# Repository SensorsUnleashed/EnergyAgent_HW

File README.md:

# EnergyAgent_HW
Used for the unleased network. Can measure energy consumption and turn on/off appliances - all done in an if/then/do kind of way

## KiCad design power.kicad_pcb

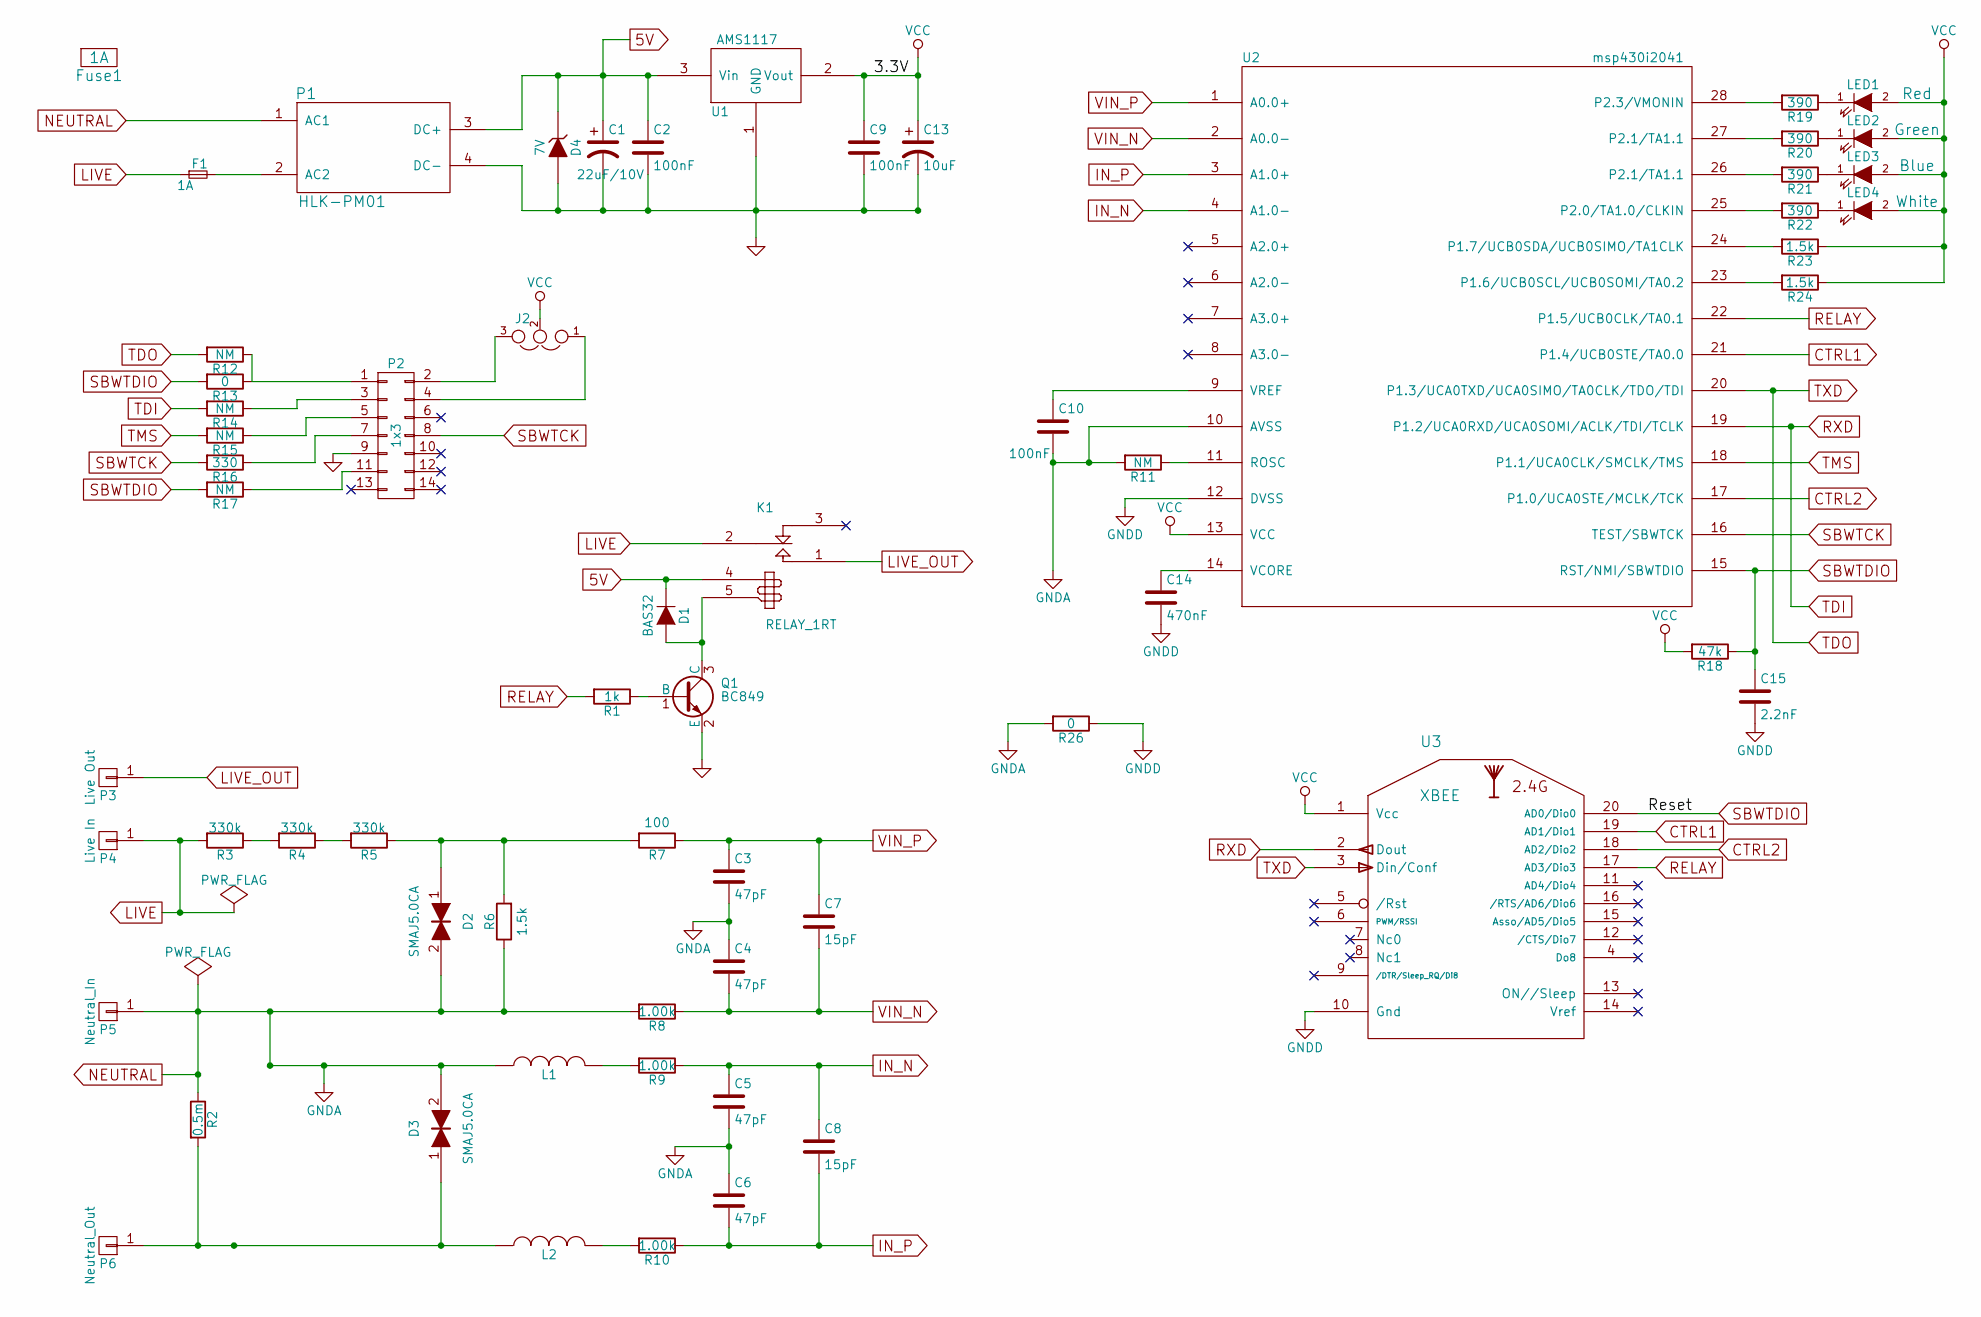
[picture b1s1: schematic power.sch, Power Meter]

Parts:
C1: 22uF/10V; C_0805
C2, C9, C10: 100nF; C_0805
C3, C4, C5, C6: 47pF; C_0805
C7, C8: 15pF; C_0805
C13: 10uF; TantalC_SizeT_EIA-3528; Manufacturer Part Number 293D106X0010B2TE3
C14: 470nF; C_0805
C15: 2.2nF; C_0805; Manufacturer Part Number 0805ZC222JAT2A
D1: BAS32; SOD-323; Manufacturer Part Number BAS321,115
D2, D3: SMAJ5.0CA; SMA_Standard; Manufacturer Part Number SMAJ5.0CA
D4: 7V; SMB_Standard; Manufacturer Part Number SMBJ7.0A-FDICT-ND
F1: 1A; Fuseholder5x20_horiz_open_Schurter_0031_8201; Manufacturer Part Number 0031.8201
Fuse1: 1A; Manufacturer Part Number 0034.3117
J2: JUMPER3; Pin_Header_Straight_1x03; Manufacturer Part Number S1011E-03-ND
K1: RELAY_1RT; Relay_SRD_XVDC-SL-C_SeriesPin4-5Swap; Manufacturer Part Number SRD-5VDC-SL-C
L1, L2: INDUCTOR; R_0805; Manufacturer Part Number BLM21BD121SN1D
LED1: LED; LED_0805; Manufacturer Part Number LTST-C170KRKT
LED2: LED; LED_0805; Manufacturer Part Number LTST-S220KGKT
LED3: LED; LED_0805; Manufacturer Part Number LTST-C170TBKT
LED4: LED4; LED_0805; Manufacturer Part Number LTW-170TK
P1: HLK-PM01
P2: 1x3; IDC_Header_Straight_14pins; Manufacturer Part Number 1-1634688-4
P3: Live Out; Banana_Jack_1Pin
P4: Live In; Banana_Jack_1Pin
P5: Neutral_In; Banana_Jack_1Pin
P6: Neutral_Out; Banana_Jack_1Pin
Q1: BC849; SOT-23
R1: 1k; R_0805
R2: 0.5m; R_2512_current_sense_4_wire; Manufacturer Part Number ULRB12512R0005FLFSLT
R3, R4, R5: 330k; R_2010; Manufacturer Part Number ERJ-S1DF3303U
R6: 1.5k; R_2010; Manufacturer Part Number MCR50JZHF1501
R7: 100; R_0805
R8, R9, R10: 1.00k; R_0805
R11, R12, R14, R15, R17: NM; R_0805
R13, R26: 0; R_0805
R16: 330; R_0805
R18: 47k; R_0805
R19, R20, R21, R22: 390; R_0805; Manufacturer Part Number ERJ-6GEYJ391V
R23, R24: 1.5k; R_0805
U1: AMS1117; SOT-223
U2: msp430i2041; TSSOP-28_4.4x9.7mm_Pitch0.65mm
U3: XBEE; XBEE-HEADER

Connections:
5V: C1.1, C2.1, D1.1 (K), D4.1 (K), K1.4, P1.3 (DC+), U1.3 (Vin)
CTRL1: U2.21 (P1.4/UCB0STE/TA0.0), U3.19 (AD1/Dio1)
CTRL2: U2.17 (P1.0/UCA0STE/MCLK/TCK), U3.18 (AD2/Dio2)
GNDD: C1.2, C2.2, C9.2, C13.2, C14.2, C15.2, D4.2 (A), P1.4 (DC-), P2.9, Q1.2 (E), R26.1, U1.1 (GND), U2.12 (DVSS), U3.10 (Gnd)
IN_N: C5.1, C8.1, R9.1, U2.4 (A1.0-)
IN_P: C6.2, C8.2, R10.1, U2.3 (A1.0+)
LIVE: F1.1, K1.2 (C1), P4.1, R3.2
LIVE_OUT: K1.1 (T1), P3.1
NEUTRAL: C3.2, C4.1, C5.2, C6.1, C10.2, D2.2, D3.2, L1.1, P1.1 (AC1), P5.1, R2.1, R6.1, R8.2, R11.2, R26.2, U2.10 (AVSS)
unnamed: C10.1, U2.9 (VREF)
unnamed: C14.1, U2.14 (VCORE)
unnamed: D1.2 (A), K1.5, Q1.3 (C)
unnamed: D2.1, R5.1, R6.2, R7.2
unnamed: D3.1, L2.1, P6.1, R2.2
unnamed: F1.2, P1.2 (AC2)
unnamed: J2.1, P2.4
unnamed: J2.3, P2.2
unnamed: L1.2, R9.2
unnamed: L2.2, R10.2
unnamed: LED1.1 (K), R19.1
unnamed: LED2.1 (K), R20.1
unnamed: LED3.1 (K), R21.1
unnamed: LED4.1 (K), R22.1
unnamed: P2.1, R12.1, R13.1
unnamed: P2.3, R14.1
unnamed: P2.5, R15.1
unnamed: P2.7, R16.1
unnamed: P2.11, R17.1
unnamed: Q1.1 (B), R1.1
unnamed: R3.1, R4.2
unnamed: R4.1, R5.2
unnamed: R11.1, U2.11 (ROSC)
unnamed: R19.2, U2.28 (P2.3/VMONIN)
unnamed: R20.2, U2.27 (P2.1/TA1.1)
unnamed: R21.2, U2.26 (P2.1/TA1.1)
unnamed: R22.2, U2.25 (P2.0/TA1.0/CLKIN)
unnamed: R23.2, U2.24 (P1.7/UCB0SDA/UCB0SIMO/TA1CLK)
unnamed: R24.2, U2.23 (P1.6/UCB0SCL/UCB0SOMI/TA0.2)
RELAY: R1.2, U2.22 (P1.5/UCB0CLK/TA0.1), U3.17 (AD3/Dio3)
RXD: R14.2, U2.19 (P1.2/UCA0RXD/UCA0SOMI/ACLK/TDI/TCLK), U3.2 (Dout)
SBWTCK: P2.8, R16.2, U2.16 (TEST/SBWTCK)
SBWTDIO: C15.1, R13.2, R17.2, R18.1, U2.15 (RST/NMI/SBWTDIO), U3.20 (AD0/Dio0)
TDO: R12.2, U2.20 (P1.3/UCA0TXD/UCA0SIMO/TA0CLK/TDO/TDI), U3.3 (Din/Conf)
TMS: R15.2, U2.18 (P1.1/UCA0CLK/SMCLK/TMS)
VCC: C9.1, C13.1, J2.2, LED1.2 (A), LED2.2 (A), LED3.2 (A), LED4.2 (A), R18.2, R23.1, R24.1, U1.2 (Vout), U2.13 (VCC), U3.1 (Vcc)
VIN_N: C4.2, C7.2, R8.1, U2.2 (A0.0-)
VIN_P: C3.1, C7.1, R7.1, U2.1 (A0.0+)

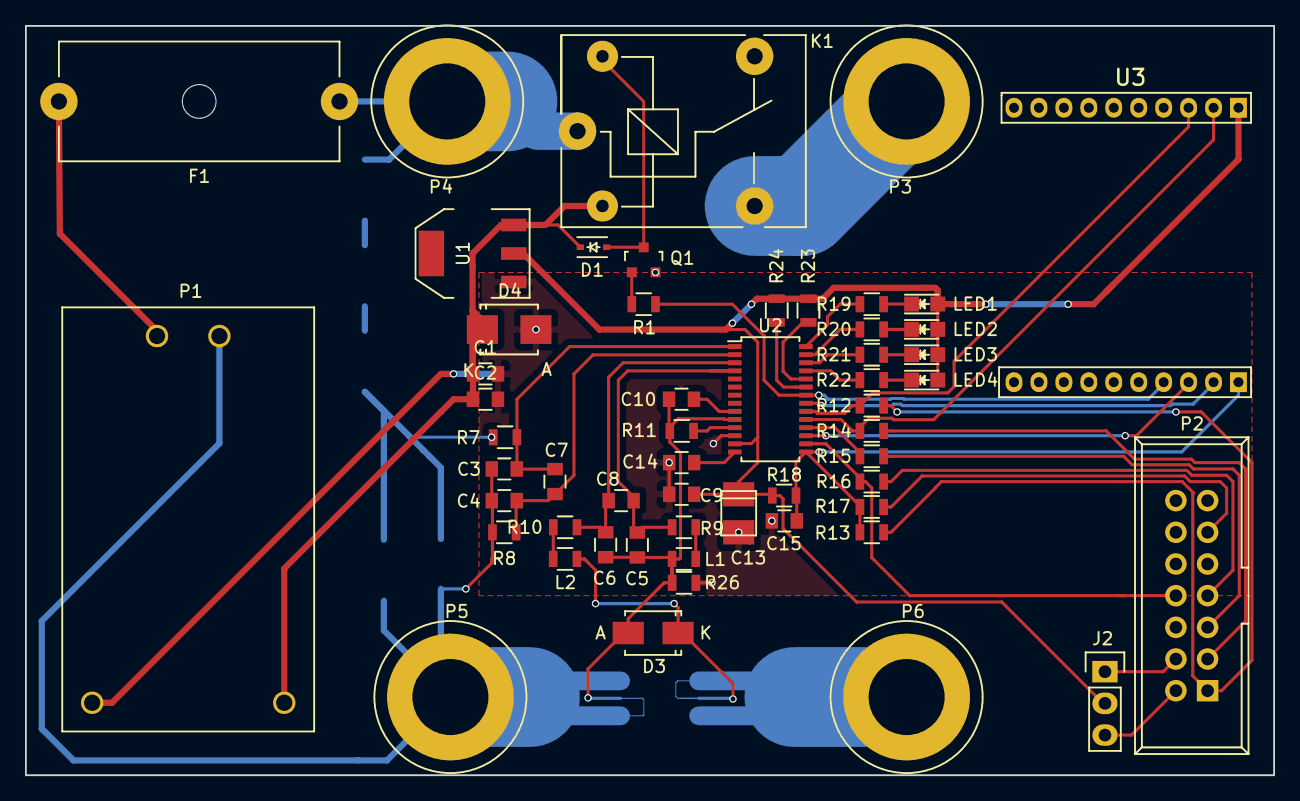
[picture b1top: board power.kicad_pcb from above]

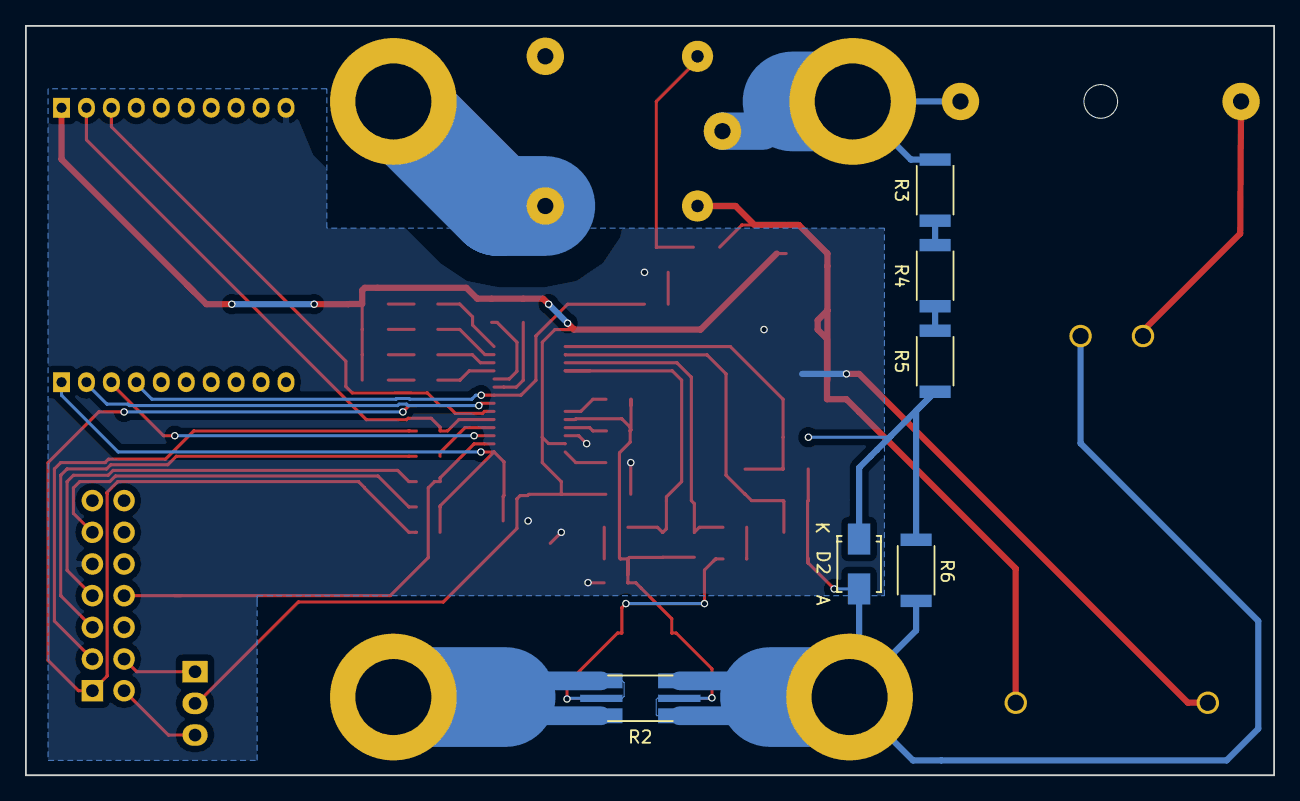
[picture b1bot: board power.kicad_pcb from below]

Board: 2 copper layers, 100.1 x 60.1 mm, 61 parts (6 on the bottom side), 47 nets.

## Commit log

2016-04-12 First commit Board should be pretty much finished. Will be send to the dirty PCB print factory.
